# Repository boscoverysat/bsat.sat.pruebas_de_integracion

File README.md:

# Prebas de Integración

## Resumen

Este repositrio contiene tanto el código como la circuitería necesaria para poder realizar la implementación del satélite.

## Elementos

### [Processing](processing/)

Contiene el código empleado para poder llevar a cabo la representación gráfica del comportamiento del satélite.

### [PCB](pcb/)

Contiene los diseños y esquemas eléctricos correspondientes a las placas de circuito impreso empleadas para el satélite.

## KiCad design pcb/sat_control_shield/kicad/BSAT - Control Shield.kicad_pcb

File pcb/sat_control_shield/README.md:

# SAT Control Shield

## Resumen

Esta sección del repositorio contiene el circuito electrónico y el diseño de placa de circuito impreso para el sistema de control del satélite.

El diseño electrónico se ha llevado a cabo mediante el software **Eagle PCB**.

#### Diseño PCB

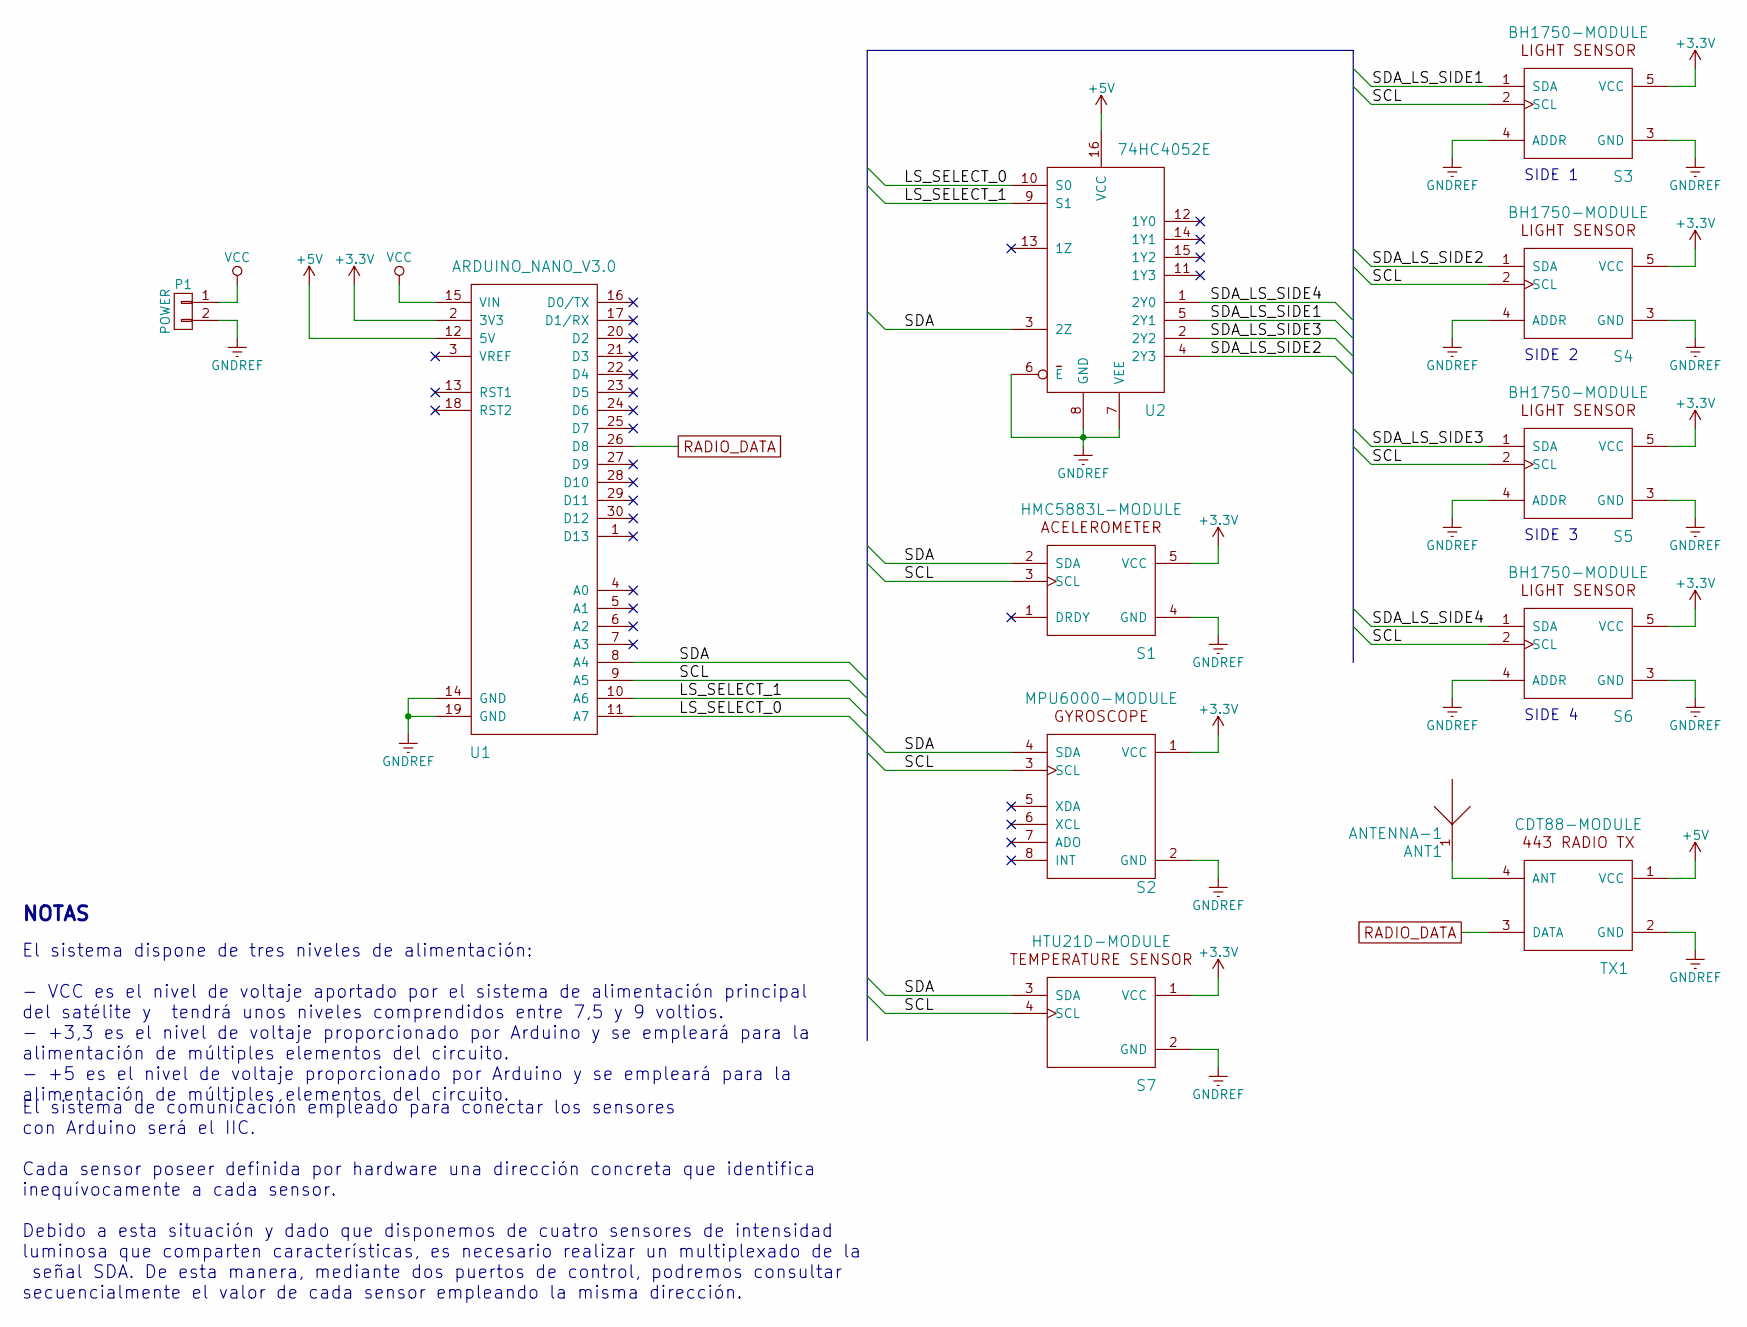
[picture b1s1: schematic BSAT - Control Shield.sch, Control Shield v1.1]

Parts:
ANT1: ANTENNA-1; Pin_Header_Angled_1x01
P1: POWER; Pin_Header_Straight_1x02
S1: HMC5883L-MODULE; HMC5883L
S2: MPU6000-MODULE; MPU-6000
S3, S4, S5, S6: BH1750-MODULE
S7: HTU21D-MODULE
TX1: CDT88-MODULE; CDT-88
U1: ARDUINO_NANO_V3.0
U2: 74HC4052E; DIP-16_W7.62mm_LongPads

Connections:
+3V3: S1.5 (VCC), S2.1 (VCC), S3.5 (VCC), S4.5 (VCC), S5.5 (VCC), S6.5 (VCC), S7.1 (VCC), U1.2 (3V3)
+5V: TX1.1 (VCC), U1.12 (5V), U2.16 (VCC)
/LS_SELECT_0: U1.11 (A7), U2.10 (S0)
/LS_SELECT_1: U1.10 (A6), U2.9 (S1)
/SCL: S1.3 (SCL), S2.3 (SCL), S3.2 (SCL), S4.2 (SCL), S5.2 (SCL), S6.2 (SCL), S7.4 (SCL), U1.9 (A5)
/SDA: S1.2 (SDA), S2.4 (SDA), S7.3 (SDA), U1.8 (A4), U2.3 (2Z)
/SDA_LS_SIDE1: S3.1 (SDA), U2.5 (2Y1)
/SDA_LS_SIDE2: S4.1 (SDA), U2.4 (2Y3)
/SDA_LS_SIDE3: S5.1 (SDA), U2.2 (2Y2)
/SDA_LS_SIDE4: S6.1 (SDA), U2.1 (2Y0)
GNDREF: P1.2, S1.4 (GND), S2.2 (GND), S3.3 (GND), S3.4 (ADDR), S4.3 (GND), S4.4 (ADDR), S5.3 (GND), S5.4 (ADDR), S6.3 (GND), S6.4 (ADDR), S7.2 (GND), TX1.2 (GND), U1.14 (GND), U1.19 (GND), U2.6 (E), U2.7 (VEE), U2.8 (GND)
unnamed: ANT1.1, TX1.4 (ANT)
RADIO_DATA: TX1.3 (DATA), U1.26 (D8)
VCC: P1.1, U1.15 (VIN)

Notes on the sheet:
SIDE 1
SIDE 2
SIDE 3
SIDE 4
NOTAS
El sistema dispone de tres niveles de alimentación: - VCC es el nivel de voltaje aportado por el sistema de alimentación principal del satélite y tendrá unos niveles comprendidos entre 7,5 y 9 voltios. - +3,3 es el nivel de voltaje proporcionado por Arduino y se empleará para la alimentación de múl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
El sistema de comunicación empleado para conectar los sensores con Arduino será el IIC. Cada sensor poseer definida por hardware una dirección concreta que identifica inequívocamente a cada sensor. Debido a esta situación y dado que disponemos de cuatro sensores de intensidad luminosa que comparten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

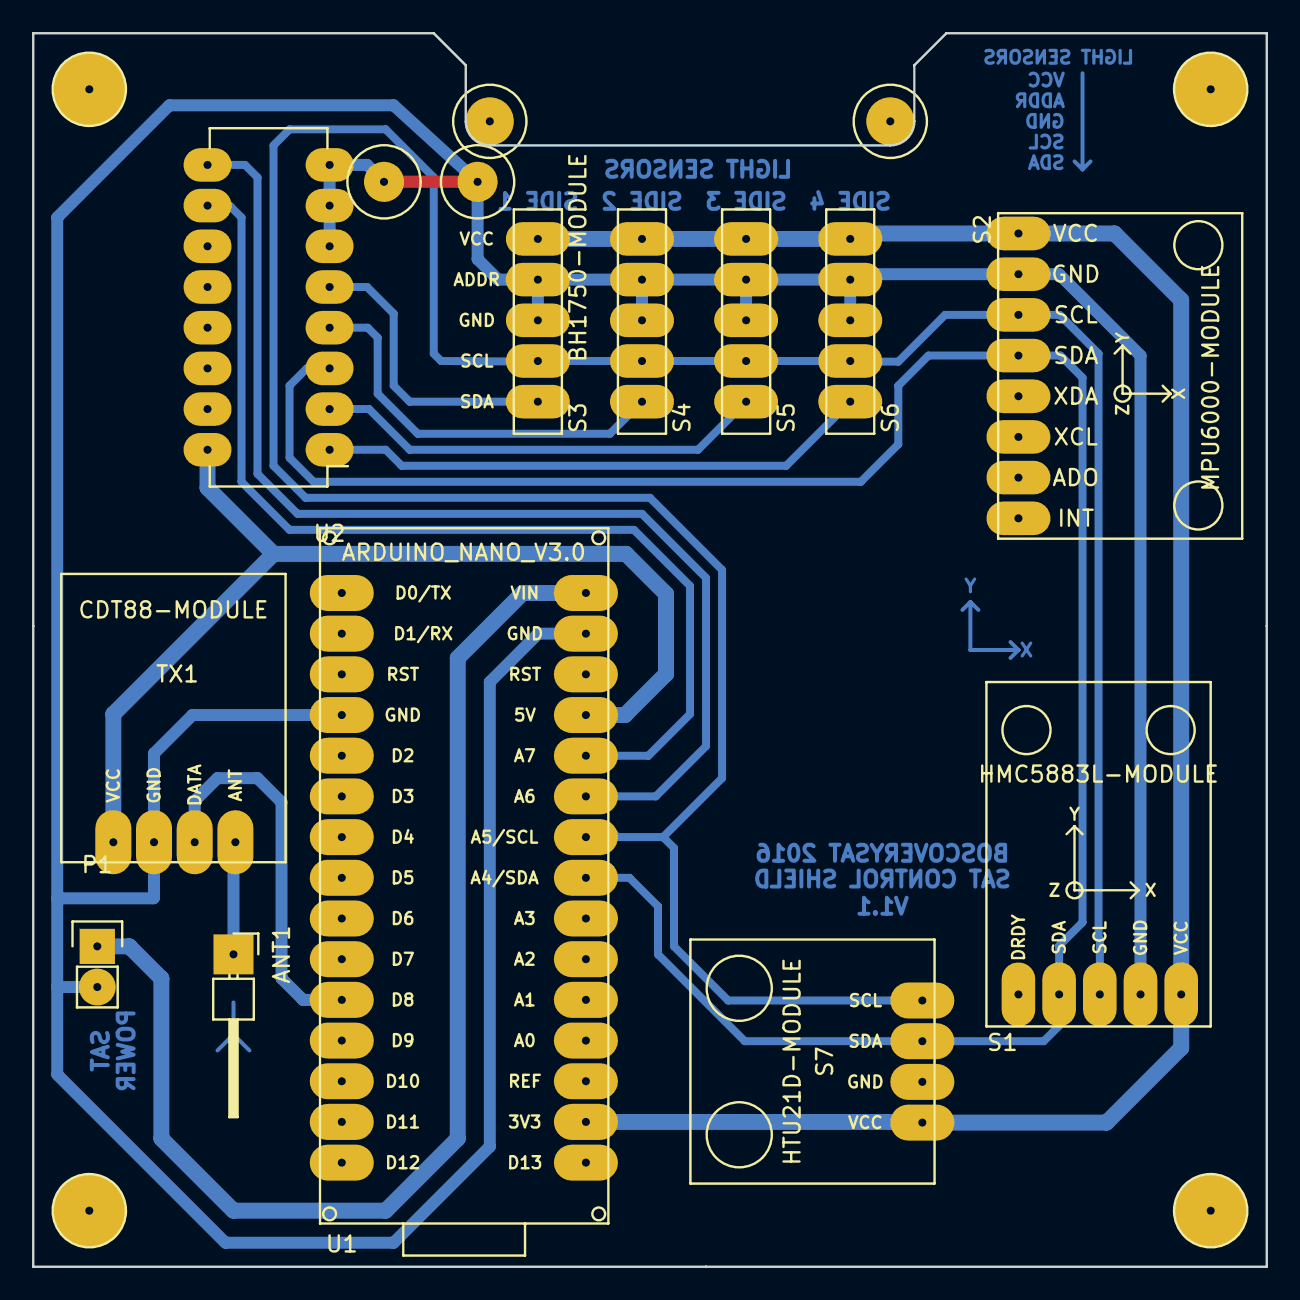
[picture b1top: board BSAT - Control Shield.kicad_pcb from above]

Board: 2 copper layers, 77.0 x 77.0 mm, 12 parts (0 on the bottom side), 14 nets.

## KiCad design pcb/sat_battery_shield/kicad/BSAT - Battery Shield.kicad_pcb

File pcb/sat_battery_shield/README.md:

# SAT Battery Shield

## Resumen

Esta sección del repositorio contiene el circuito electrónico y el diseño de placa de circuito impreso para el sistema de alimentación del satélite.

El diseño electrónico se ha llevado a cabo mediante el software **Eagle PCB**.

#### Diseño PCB

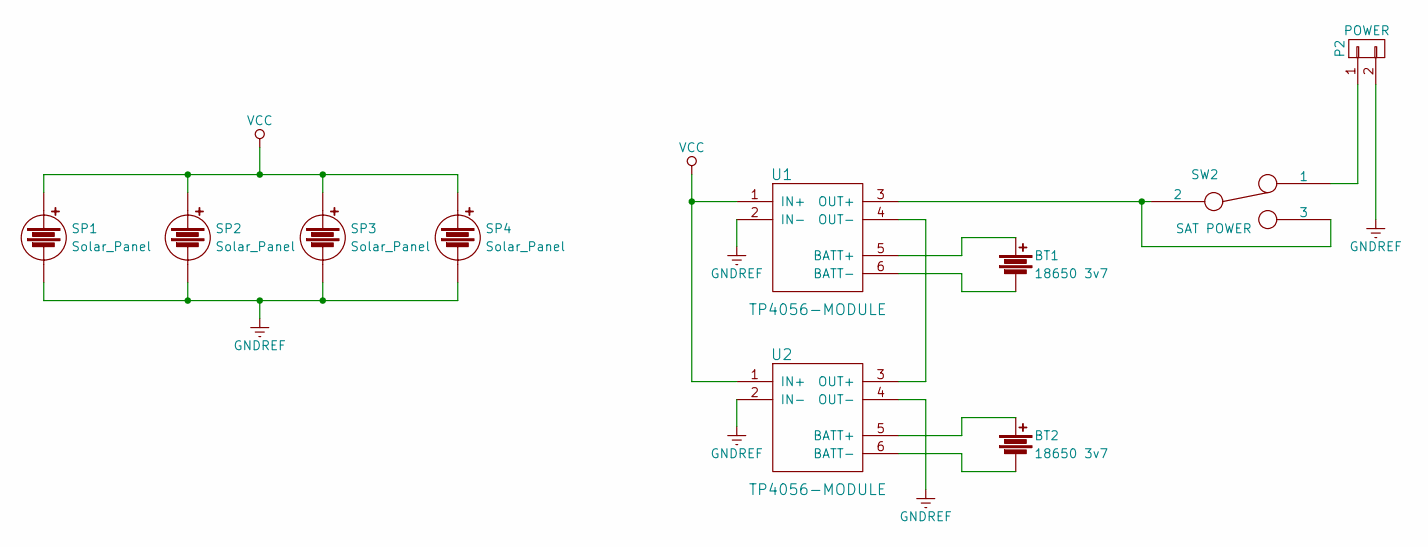
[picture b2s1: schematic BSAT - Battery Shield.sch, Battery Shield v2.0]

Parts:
BT1, BT2: 18650 3v7; BATT-18650
P2: POWER; Pin_Header_Straight_1x02
SP1, SP2, SP3, SP4: Solar_Panel; Pin_Header_Straight_1x02
SW2: SAT POWER; SWITCH-1CIR-2CON
U1, U2: TP4056-MODULE

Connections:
GNDREF: P2.2, SP1.2, SP2.2, SP3.2, SP4.2, U1.2 (IN-), U2.2 (IN-), U2.4 (OUT-)
unnamed: BT1.1, U1.5 (BATT+)
unnamed: BT1.2, U1.6 (BATT-)
unnamed: BT2.1, U2.5 (BATT+)
unnamed: BT2.2, U2.6 (BATT-)
unnamed: P2.1, SW2.1
unnamed: SW2.2, SW2.3, U1.3 (OUT+)
unnamed: U1.4 (OUT-), U2.3 (OUT+)
VCC: SP1.1, SP2.1, SP3.1, SP4.1, U1.1 (IN+), U2.1 (IN+)

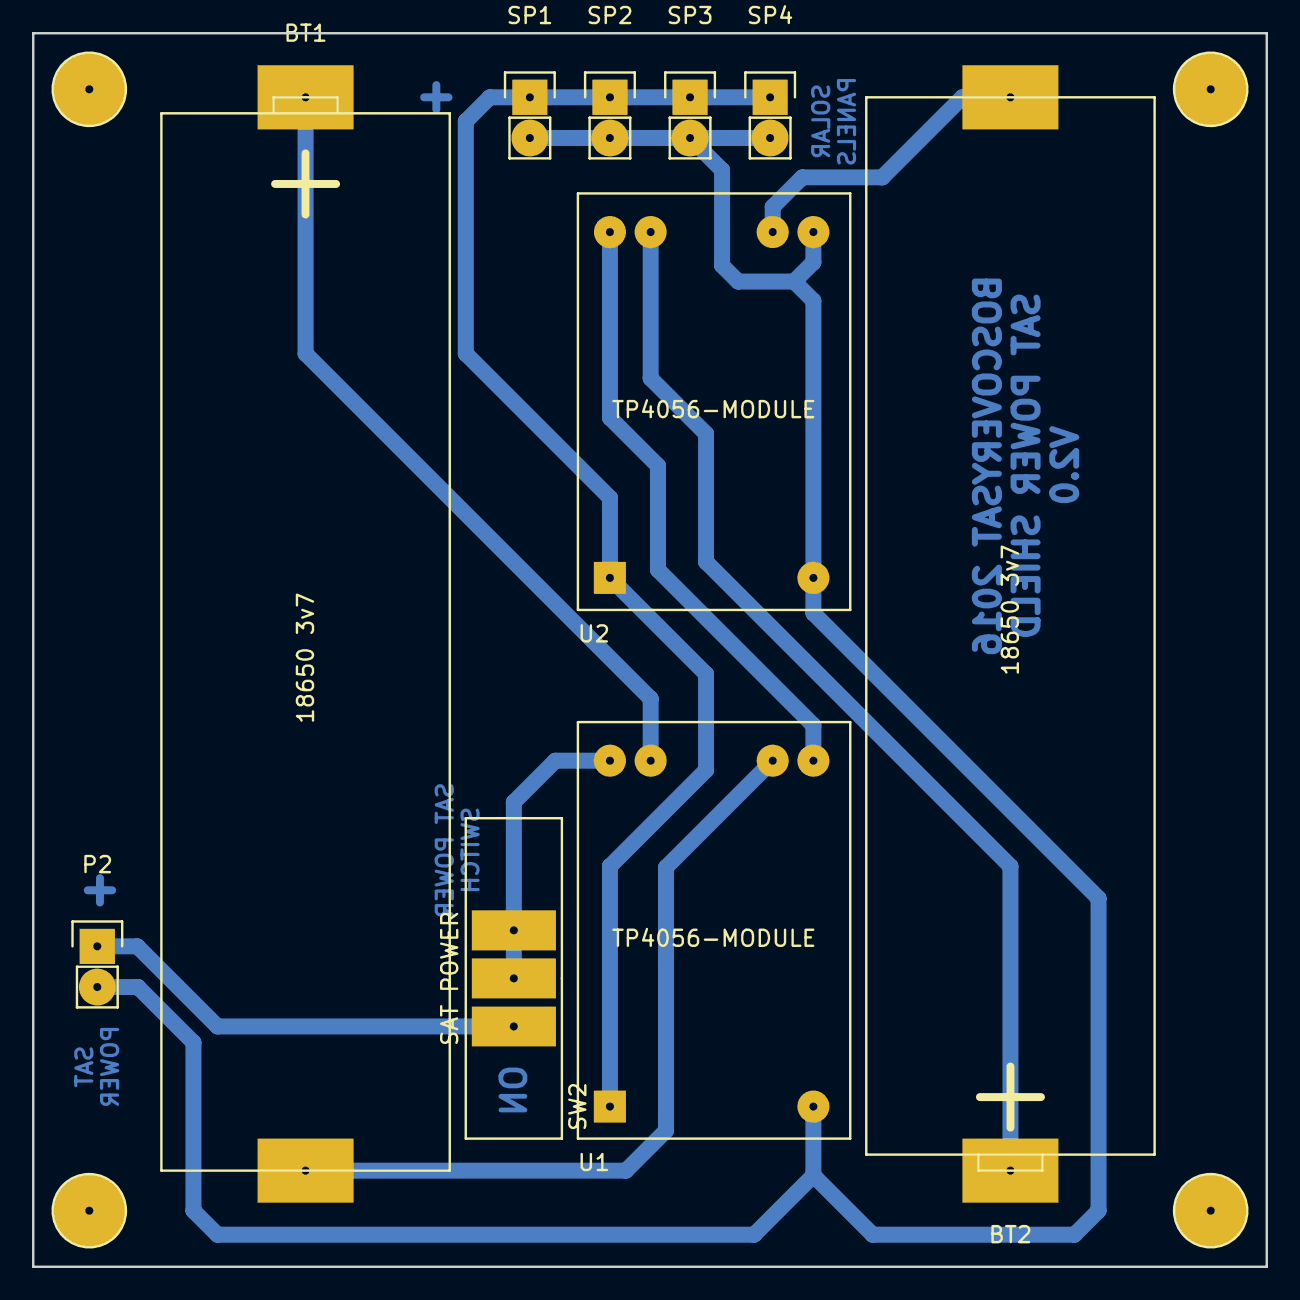
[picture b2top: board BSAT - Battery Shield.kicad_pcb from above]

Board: 2 copper layers, 77.0 x 77.0 mm, 10 parts (0 on the bottom side), 9 nets.

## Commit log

2015-11-07 Prototipo en desarrollo del software de Telemetría
2015-11-13 Con datos de prueba
2015-11-16 [ FEATURE ] - Añadidos esquemas y PCBs de satélite y receptor de RF.
2015-11-16 [ UPDATE ] - Actualizada imagen del PCB para el receptor de RF.
2015-11-16 Actualizado el Software
2015-11-17 Añadidos logos y zona para la representación 3D
2015-11-18 Software Estación de Tierra
2015-11-18 Añadida la carpeta Arduino
2015-11-20 [ UPDATE ] - Añadiendo procesamiento de telemetría mediante NodeJS.
2015-11-20 [ REPO CONFIG ] - Añadido archivo .gitignore.
2015-11-20 [ REPO UPDATE ] - Carpeta de módulos de NodeJS eliminada.
2015-11-20 [ UPDATE ] - Archivo package.json editado.
2016-05-25 feat(battery-shield): Diseños basados en KiCAD añadidos.
2016-05-26 chore(gitignore): File updated in order to avoid track .DS_Store files.
2016-05-26 chore(boscoverysat-lib): Arduino Nano V3.0 and 443 transmisor schema symbols attached.
2016-05-26 feat(control-shield): KiCAD project created for this shield.
2016-05-27 chore(desktop-app): Working on.
2016-05-27 feat(boscoverysat-lib): Library edited.
2016-05-27 feat(control-shield): Working on.
2016-05-29 feat(boscoverysat-lib): Arduino Nano v3, sensor luminos BH1750 y emisor de radio CDT-88 añadidos a la librería.
2016-05-29 refactor(battery-shield): Esquema actualizado.
2016-05-29 refactor(control-shield): Esquema y PCB rediseñadas a la versión v1.1 mediante KiCAD.
2016-05-30 feat(boscoverysat-lib): Sensor de temperatura HTU21D añadido.
2016-05-30 feat(control-shield): Sensor de temperatura HTU21D añadido.
2016-06-03 chore(local): Actualización repositorio local
